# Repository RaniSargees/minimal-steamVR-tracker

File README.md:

# minimal-steamVR-tracker
a bare-minimum hand-solderable steamVR tracker, based on http://hivetracker.github.io/

The firmware for this does not yet exist.

Arduino is incompatible with the nrf52810, so this design does not work with the hivetracker firmware. This can be changed by replacing the [Laird bl651](https://www.lairdconnect.com/wireless-modules/bluetooth-modules/bluetooth-5-modules/bl651-series-bluetooth-module) module with the compatible nrf52832-based [Laird bl652](https://www.lairdconnect.com/wireless-modules/bluetooth-modules/bluetooth-5-modules/bl652-series-bluetooth-v5-nfc-module). The design does not need to be changed.

Additionally, the IMU has been changed from the BNO055 to the *much* cheaper MPU-6050. If using the hivetracker firmware, it will need to be modified to support this different IMU.

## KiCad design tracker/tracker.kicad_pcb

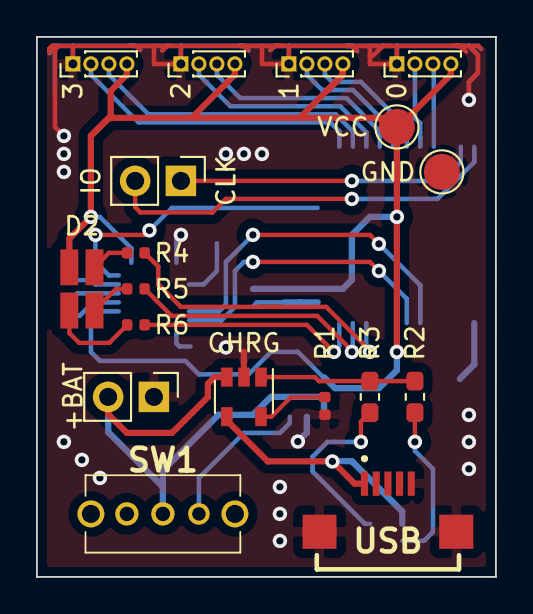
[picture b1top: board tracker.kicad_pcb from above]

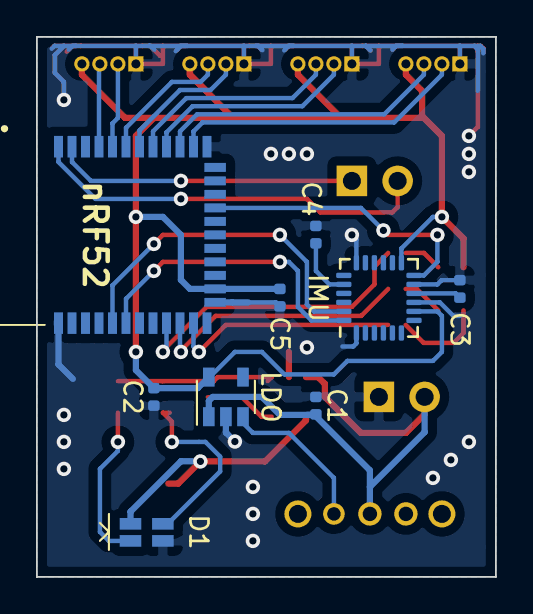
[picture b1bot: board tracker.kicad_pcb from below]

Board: 2 copper layers, 25.5 x 30.0 mm, 27 parts (9 on the bottom side), 30 nets.

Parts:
0: Chiclet0; PinHeader_1x04_P1.00mm_Vertical
1: Chiclet1; PinHeader_1x04_P1.00mm_Vertical
2: Chiclet2; PinHeader_1x04_P1.00mm_Vertical
3: Chiclet3; PinHeader_1x04_P1.00mm_Vertical
+BAT: Battery; PinHeader_1x02_P2.54mm_Vertical
C1, C2, C5: 1uf; C_0402_1005Metric
C3: 0.1uf; C_0402_1005Metric
C4: 2.2nf; C_0402_1005Metric
CHRG: MCP73831-2-OT; SOT-23-5
D1: LED_Dual_AACC; 1616LED
D2: LED_BGRA; 0404LED
GND: TestPoint; TestPoint_Pad_D2.0mm
IMU: MPU-6050; InvenSense_QFN-24_4x4mm_P0.5mm
J7: SWD; PinHeader_1x02_P2.54mm_Vertical
LDO: MIC5504-3.3YM5; SOT-23-5
R1: 2K; R_0402_1005Metric
R2, R3: 330; C_0603_1608Metric_Pad1.05x0.95mm_HandSolder
R4: 300; R_0402_1005Metric
R5, R6: 82; R_0402_1005Metric
SW1: Power Switch; 18252321
USB: USB_B_Micro; 101181920001LF
VCC: TestPoint; TestPoint_Pad_D2.0mm
nRF52: 453-00005; 45300005

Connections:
+BATT: +BAT.2, C1.2, CHRG.3, LDO.1, SW1.2
B: R6.2, nRF52.29
D0: 0.2, nRF52.9
D1: 1.2, nRF52.11
D2: 2.2, nRF52.13
D3: 3.2, nRF52.15
E0: 0.3, nRF52.8
E1: 1.3, nRF52.10
E2: 2.3, nRF52.12
E3: 3.3, nRF52.14
G: R5.2, nRF52.30
GND: 0.1, 1.1, 2.1, 3.1, +BAT.1, C1.1, C2.1, C3.2, C4.2, C5.1, CHRG.2, D1.4, GND.1, IMU.1, IMU.9, IMU.11, IMU.18, LDO.2, R1.1, USB.5, USB.6, nRF52.16, nRF52.27, nRF52.39
INT1: IMU.12, nRF52.20
unnamed: C3.1, IMU.10
unnamed: C4.1, IMU.20
unnamed: D1.2, R2.2
unnamed: D1.3, R3.1
unnamed: D2.1, R6.1
unnamed: D2.2, R5.1
unnamed: D2.3, R4.1
unnamed: J7.2, nRF52.5
unnamed: J7.1, nRF52.6
unnamed: CHRG.5, R1.2
unnamed: CHRG.1, R2.1, R3.2
unnamed: LDO.3, SW1.3
R: R4.2, nRF52.31
SCL: IMU.23, nRF52.35
SDA: IMU.24, nRF52.34
VBUS: CHRG.4, D1.1, USB.1
VCC: 0.4, 1.4, 2.4, 3.4, C2.2, C5.2, D2.4, IMU.8, IMU.13, LDO.5, VCC.1, nRF52.26

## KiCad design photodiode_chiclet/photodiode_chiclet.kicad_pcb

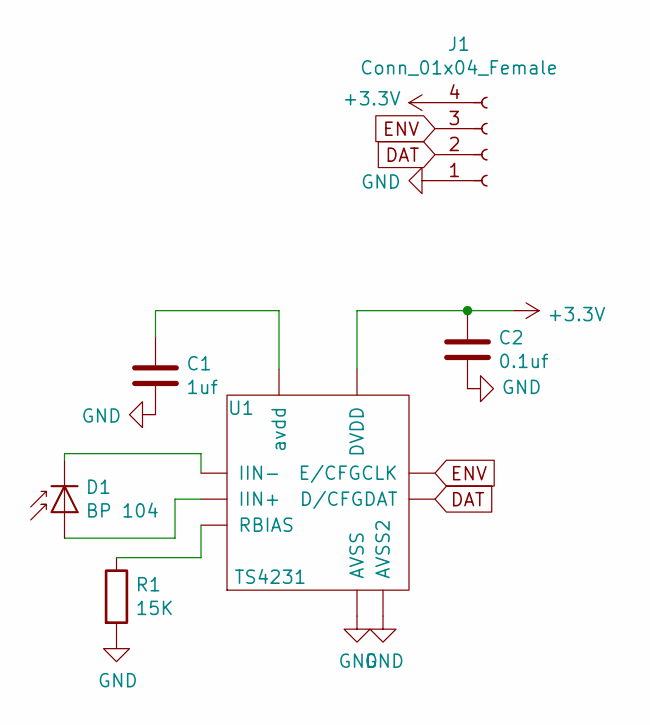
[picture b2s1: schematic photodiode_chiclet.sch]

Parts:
C1: 1uf; C_0402_1005Metric
C2: 0.1uf; C_0402_1005Metric
D1: BP 104; DIO_BP_104_S-Z
J1: Conn_01x04_Female; PinHeader_1x04_P1.00mm_Horizontal
R1: 15K; R_0402_1005Metric
U1: TS4231

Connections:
+3V3: C2.1, J1.4, U1.C3 (DVDD)
DAT: J1.2, U1.C1 (D/CFGDAT)
ENV: J1.3, U1.C2 (E/CFGCLK)
GND: C1.2, C2.2, J1.1, R1.2, U1.B2 (AVSS)
unnamed: C1.1, U1.A1 (avdd)
unnamed: D1.1 (K), U1.A3 (IIN-)
unnamed: D1.2 (A), U1.A2 (IIN+)
unnamed: R1.1, U1.B1 (RBIAS)

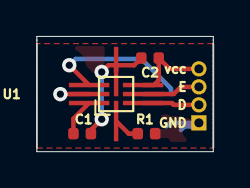
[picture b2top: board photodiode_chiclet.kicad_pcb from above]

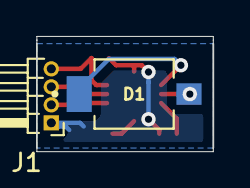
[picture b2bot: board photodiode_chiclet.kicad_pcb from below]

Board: 2 copper layers, 9.8 x 6.4 mm, 6 parts (2 on the bottom side), 8 nets.

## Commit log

2021-01-30 add chiclet photodiode board design
2021-02-01 add main tracking board designs
